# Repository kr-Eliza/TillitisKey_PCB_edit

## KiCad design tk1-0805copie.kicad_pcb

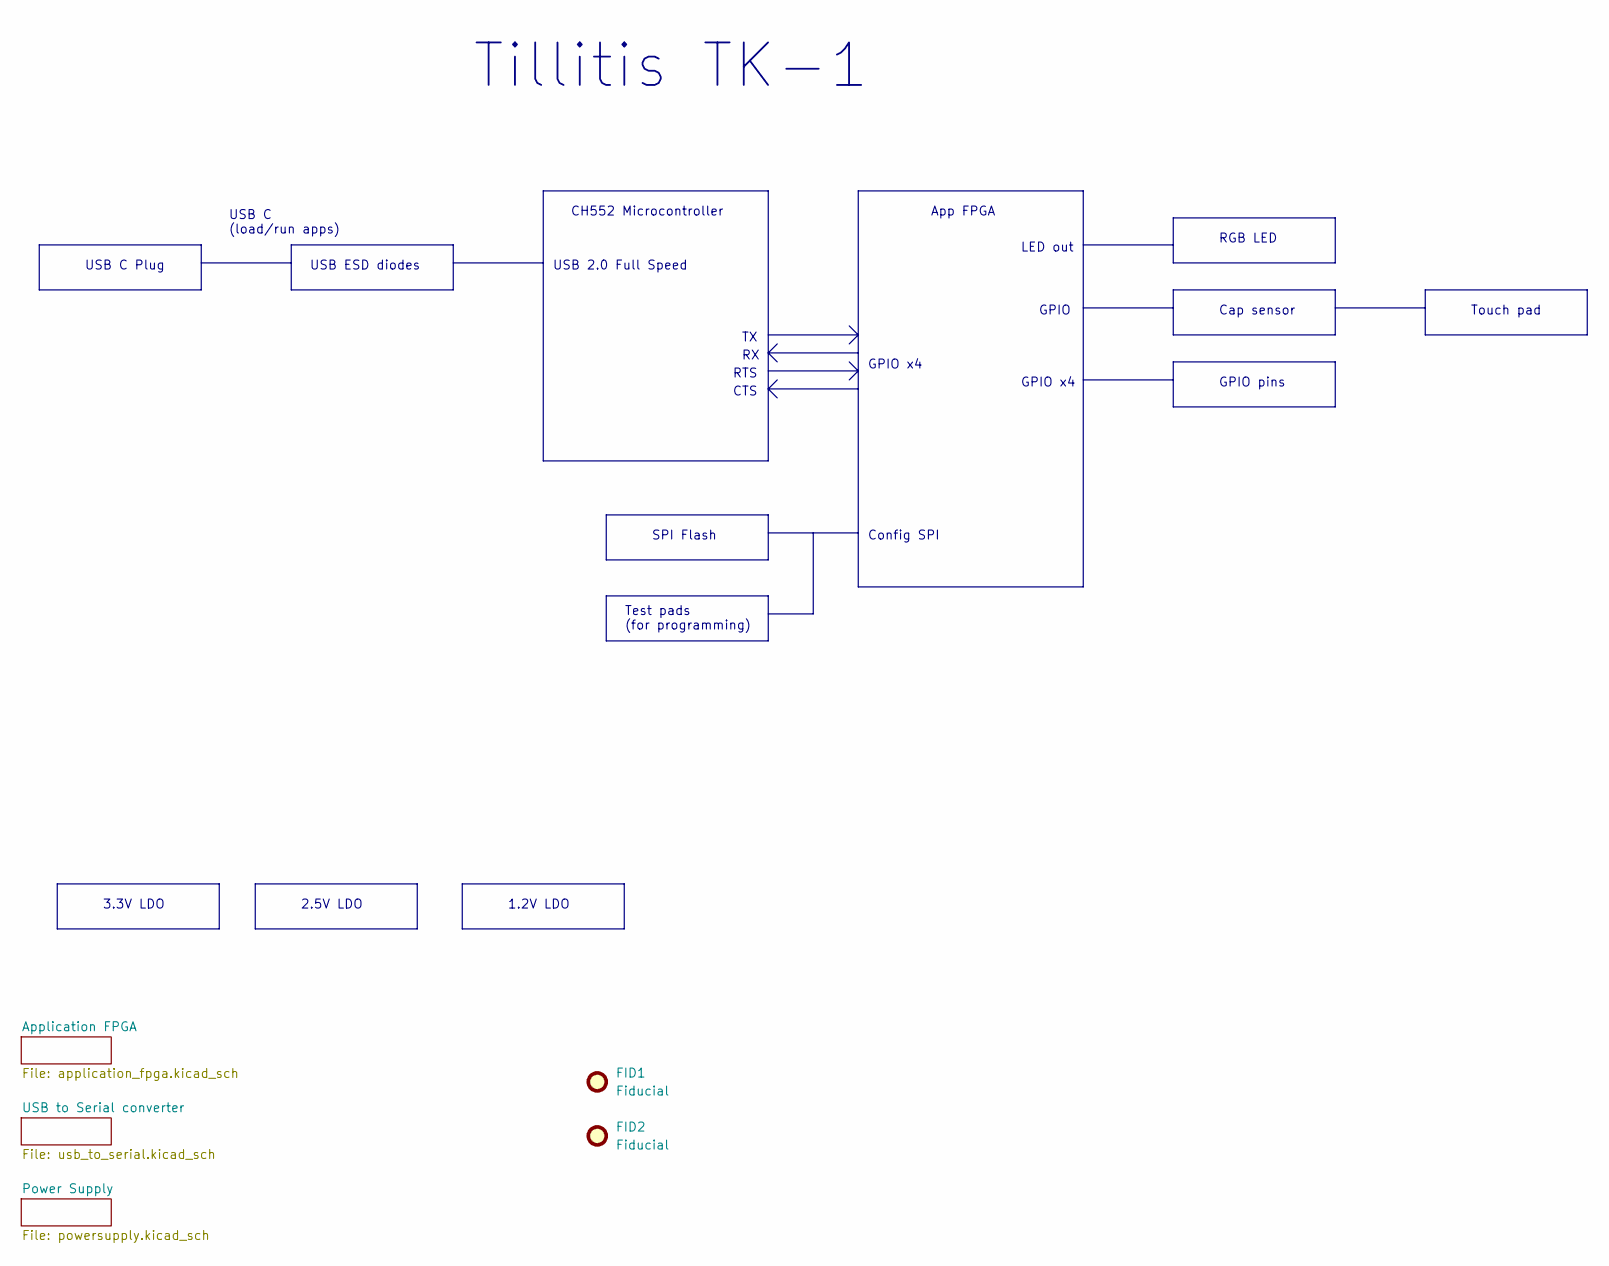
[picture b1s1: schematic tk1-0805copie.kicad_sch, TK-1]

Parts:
FID1, FID2: Fiducial; Fiducial_0.75mm_Mask1.5mm

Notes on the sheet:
USB ESD diodes
Touch pad
GPIO x4
GPIO pins
Cap sensor
USB 2.0 Full Speed
RTS
USB C Plug
CH552 Microcontroller
RGB LED
USB C (load/run apps)
1.2V LDO
3.3V LDO
CTS
2.5V LDO
App FPGA
Config SPI
Tillitis TK-1
SPI Flash
GPIO
LED out
Test pads (for programming)

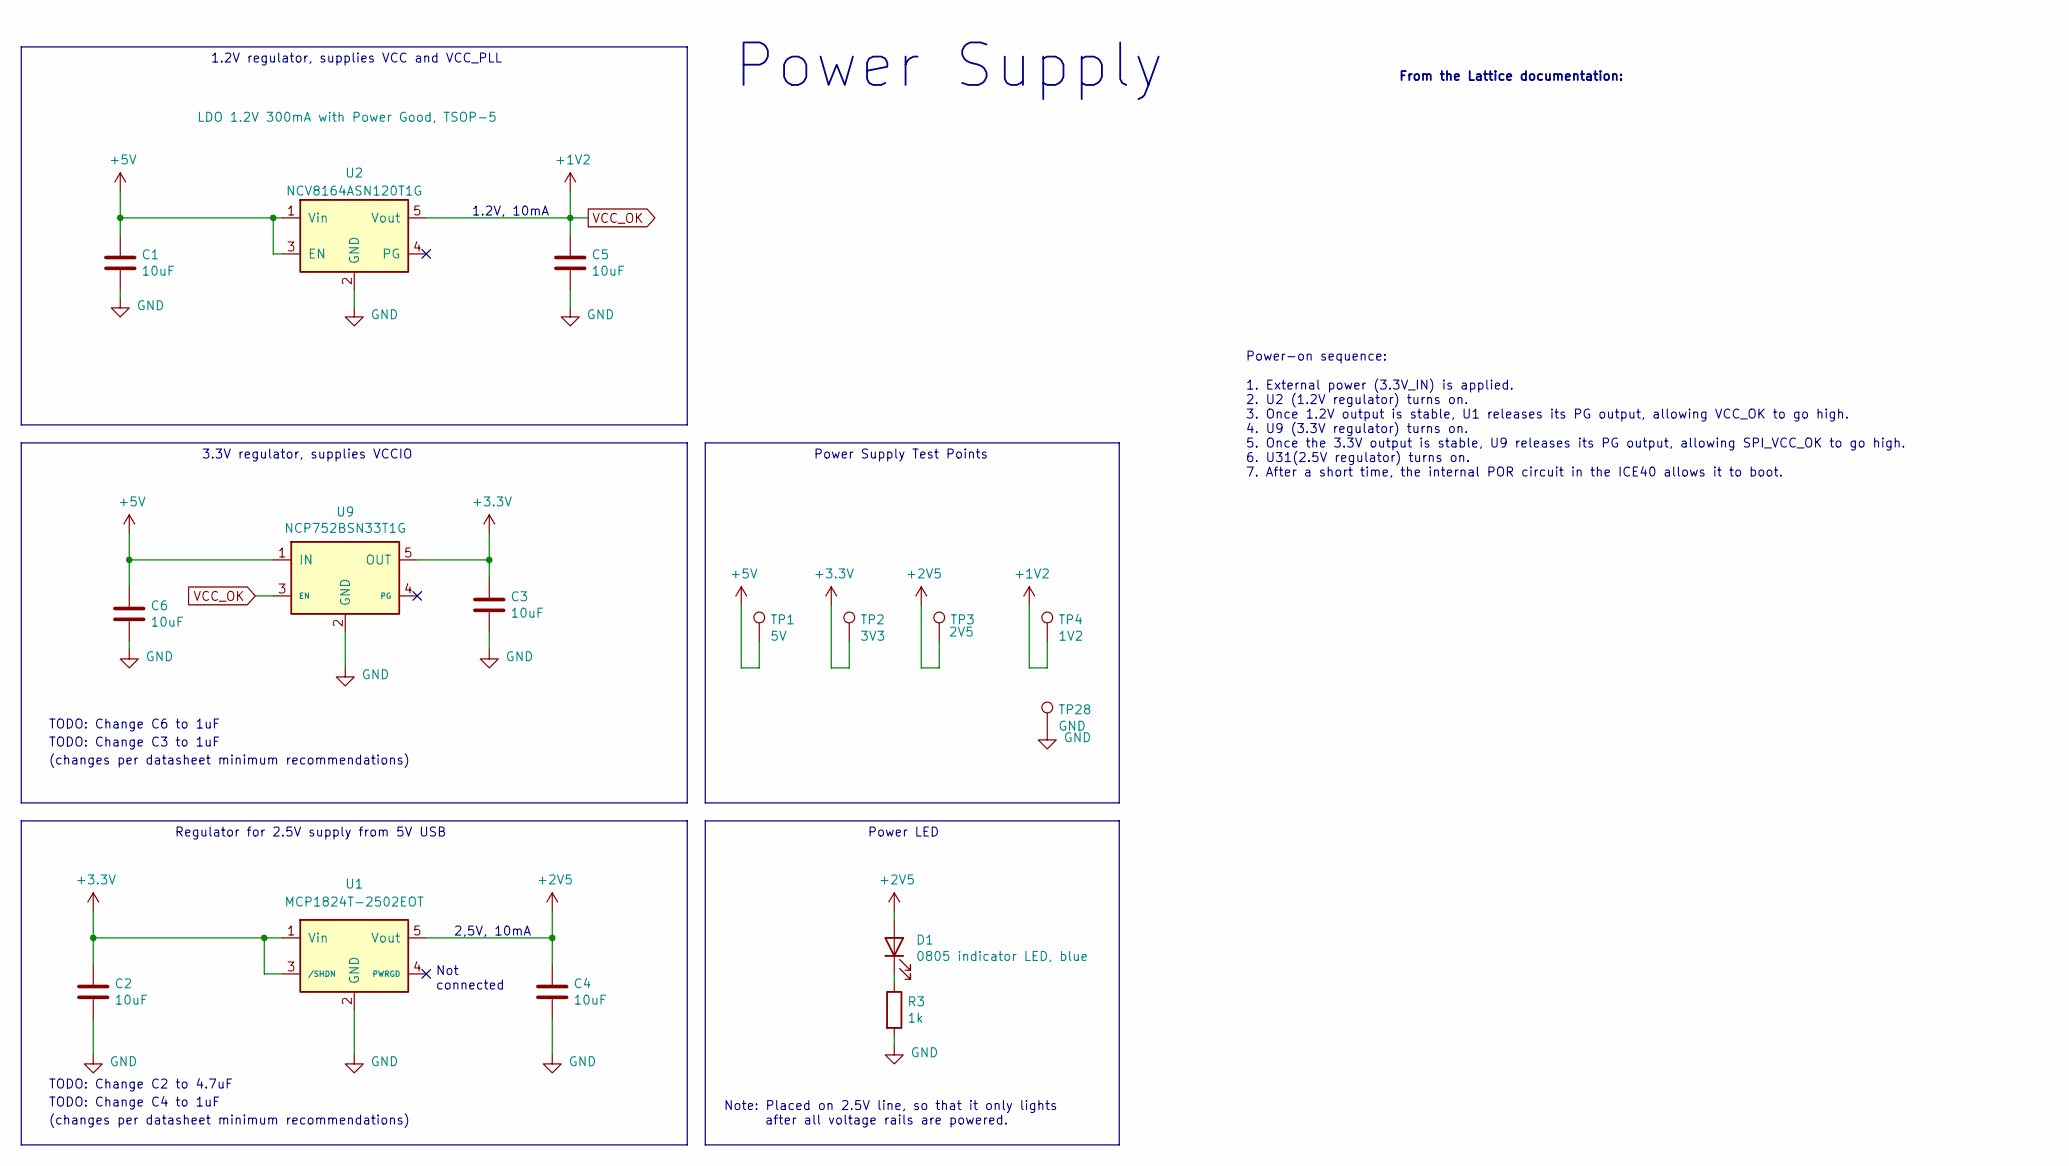
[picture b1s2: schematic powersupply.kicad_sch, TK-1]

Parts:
C1, C2, C3, C4, C5, C6: 10uF; C_0805_2012Metric_Pad1.18x1.45mm_HandSolder; Manufacturer Part Number CL21A106KPFNNNE; Mouser Part Number 187-CL21A106KPFNNNE
D1: 0805 indicator LED, blue; LED_0805_2012Metric_Pad1.15x1.40mm_HandSolder; Manufacturer Part Number LTST-S220TBKT; Mouser Part Number 859-LTST-S220TBKT
R3: 1k; R_0805_2012Metric_Pad1.20x1.40mm_HandSolder; Manufacturer Part Number RC0805FR-071KL; Mouser Part Number 603-RC0805FR-071KL
TP1: 5V; TestPoint_Pad_D1.0mm
TP2: 3V3; TestPoint_Pad_D1.0mm
TP3: 2V5; TestPoint_Pad_D1.0mm
TP4: 1V2; TestPoint_Pad_D1.0mm
TP28: GND; TestPoint_Pad_D1.0mm
U1: MCP1824T-2502EOT; SOT-23-5; Manufacturer Part Number MCP1824T-2502E/OT; Mouser Part Number 579-MCP1824T-2502E/OT
U2: NCV8164ASN120T1G; TSOP-5_1.65x3.05mm_P0.95mm; Manufacturer Part Number NCV8164ASN120T1G; Mouser Part Number 863-NCV8164ASN120T1G
U9: NCP752BSN33T1G; Manufacturer Part Number NCP752BSN33T1G; Mouser Part Number 863-NCP752BSN33T1G

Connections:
+2V5: C4.1, D1.2 (A), TP3.1, U1.5 (Vout); also elsewhere on the board
+3.3V: C2.1, C3.1, TP2.1, U1.1 (Vin), U1.3 (/SHDN), U9.5 (OUT); also elsewhere on the board
+5V: C1.1, C6.1, TP1.1, U2.1 (Vin), U2.3 (EN), U9.1 (IN); also elsewhere on the board
GND: C1.2, C2.2, C3.2, C4.2, C5.2, C6.2, R3.2, TP28.1, U1.2 (GND), U2.2 (GND), U9.2 (GND); also elsewhere on the board
unnamed: D1.1 (K), R3.1
VCC_OK: C5.1, TP4.1, U2.5 (Vout), U9.3 (EN); also elsewhere on the board

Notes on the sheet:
Power-on sequence: 1. External power (3.3V_IN) is applied. 2. U2 (1.2V regulator) turns on. 3. Once 1.2V output is stable, U1 releases its PG output, allowing VCC_OK to go high. 4. U9 (3.3V regulator) turns on. 5. Once the 3.3V output is stable, U9 releases its PG output, allowing SPI_VCC_OK to go 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
TODO: Change C2 to 4.7uF
(changes per datasheet minimum recommendations)
TODO: Change C6 to 1uF
2,5V, 10mA
Note: Placed on 2.5V line, so that it only lights after all voltage rails are powered.
TODO: Change C3 to 1uF
1.2V, 10mA
Power Supply
From the Lattice documentation:
1.2V regulator, supplies VCC and VCC_PLL
3.3V regulator, supplies VCCIO
TODO: Change C4 to 1uF
Not connected
Power Supply Test Points
Power LED
Regulator for 2.5V supply from 5V USB

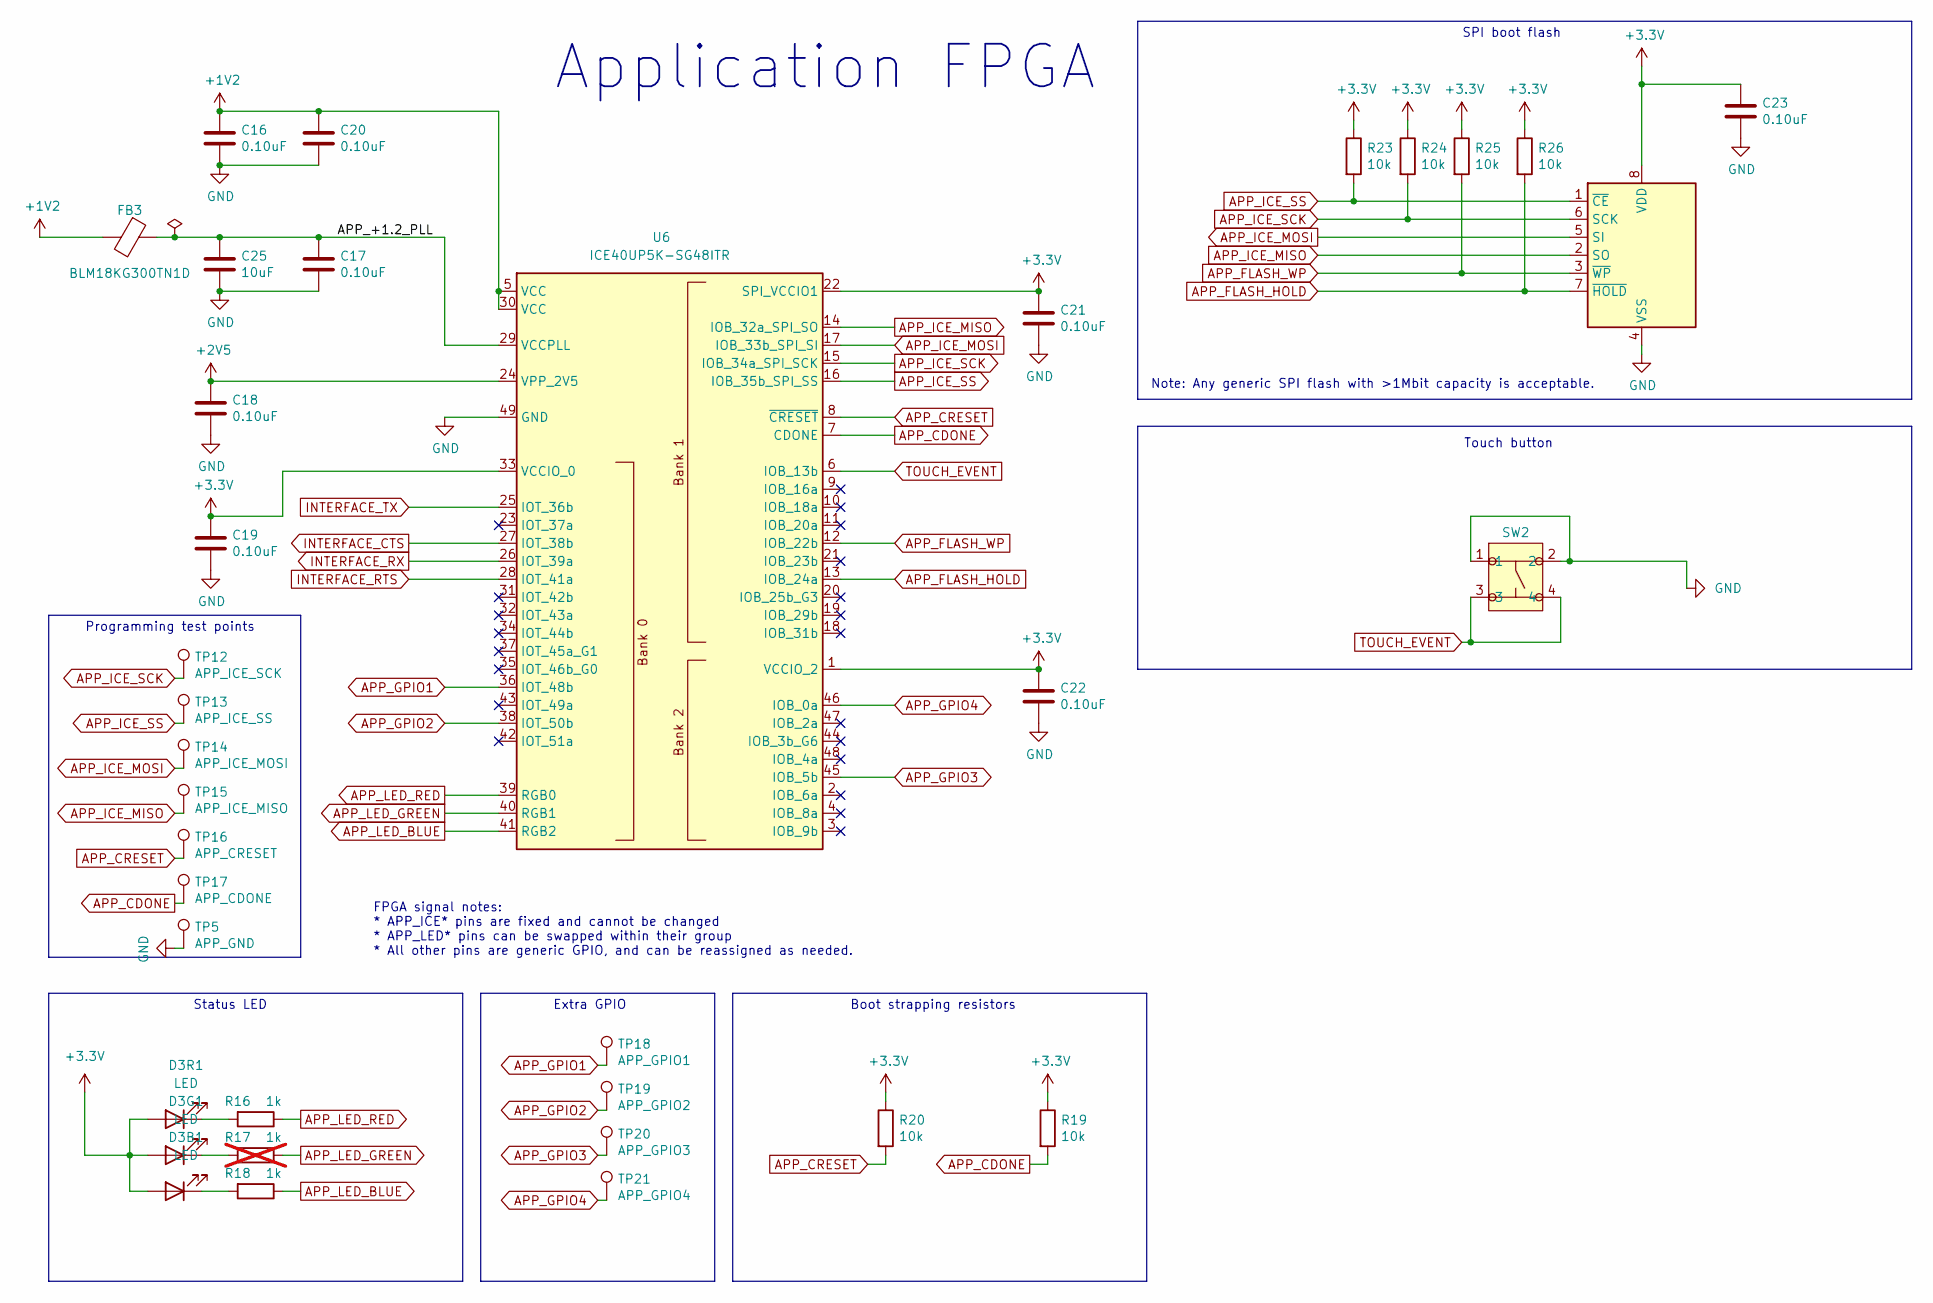
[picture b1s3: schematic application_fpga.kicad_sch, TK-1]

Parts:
C16, C17, C18, C19, C20, C21, C22, C23: 0.10uF; C_0805_2012Metric_Pad1.18x1.45mm_HandSolder; Manufacturer Part Number C0805C104K5RACTU; Mouser Part Number 80-C0805C104K5R
C25: 10uF; C_0805_2012Metric_Pad1.18x1.45mm_HandSolder; Manufacturer Part Number CL21A106KPFNNNE; Mouser Part Number 187-CL21A106KPFNNNE
D3B1: LED; LED_0805_2012Metric_Pad1.15x1.40mm_HandSolder; Manufacturer Part Number LTST-S220TBKT; Mouser Part Number 859-LTST-S220TBKT
D3G1: LED; LED_0805_2012Metric_Pad1.15x1.40mm_HandSolder; Manufacturer Part Number LTST-S270KGKT; Mouser Part Number 859-LTST-S270KGKT
D3R1: LED; LED_0805_2012Metric_Pad1.15x1.40mm_HandSolder; Manufacturer Part Number LTST-S270KRKT; Mouser Part Number 859-LTST-S270KRKT
FB3: BLM18KG300TN1D; Ferritbead_0603_1608Metric; Manufacturer Part Number BLM18KG300TN1D; Mouser Part Number 81-BLM18KG300TN1D
R16, R18: 1k; R_0805_2012Metric_Pad1.20x1.40mm_HandSolder; Manufacturer Part Number RC0805FR-071KL; Mouser Part Number 603-RC0805FR-071KL
R17: 1k; R_0805_2012Metric_Pad1.20x1.40mm_HandSolder; Manufacturer Part Number RC0805FR-071KL; Mouser Part Number 603-RC0805FR-071KL; not fitted
R19, R20, R23, R24, R25, R26: 10k; R_0805_2012Metric; Manufacturer Part Number RC0805FR-0710KL; Mouser Part Number 603-RC0805FR-0710KL
SW2: PTS526_SK15_SMTR2_LFS; PTS526SK15SMTR2LFS; Manufacturer_Part_Number PTS526 SK15 SMTR2 LFS; Mouser Part Number 611-PTS526SK15SMR2L
TP5: APP_GND; TestPoint_Pad_D1.0mm
TP12: APP_ICE_SCK; TestPoint_Pad_D1.0mm
TP13: APP_ICE_SS; TestPoint_Pad_D1.0mm
TP14: APP_ICE_MOSI; TestPoint_Pad_D1.0mm
TP15: APP_ICE_MISO; TestPoint_Pad_D1.0mm
TP16: APP_CRESET; TestPoint_Pad_D1.0mm
TP17: APP_CDONE; TestPoint_Pad_D1.0mm
TP18: APP_GPIO1; TestPoint_Pad_D1.0mm
TP19: APP_GPIO2; TestPoint_Pad_D1.0mm
TP20: APP_GPIO3; TestPoint_Pad_D1.0mm
TP21: APP_GPIO4; TestPoint_Pad_D1.0mm
U4: SST25VF080B-50-4x-S2Ax; SOIC-8_3.9x4.9mm_P1.27mm
U6: ICE40UP5K-SG48ITR; QFN-48-1EP_7x7mm_P0.5mm_EP5.3x5.3mm; Manufacturer Part Number ICE40UP5K-SG48I; Mouser Part Number 842-ICE40UP5K-SG48I

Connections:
+2V5: C18.1, U6.24 (VPP_2V5); also elsewhere on the board
+3.3V: C19.1, C21.1, C22.1, C23.1, D3B1.2 (A), D3G1.2 (A), D3R1.2 (A), R19.1, R20.1, R23.1, R24.1, R25.1, R26.1, U4.8 (VDD), U6.1 (VCCIO_2), U6.22 (SPI_VCCIO1), U6.33 (VCCIO_0); also elsewhere on the board
/Application FPGA/APP_+1.2_PLL: C17.1, C25.1, FB3.1, U6.29 (VCCPLL)
APP_CDONE: R19.2, TP17.1, U6.7 (CDONE)
APP_CRESET: R20.2, TP16.1, U6.8 (~CRESET)
APP_FLASH_HOLD: R26.2, U4.7 (~HOLD), U6.13 (IOB_24a)
APP_FLASH_WP: R25.2, U4.3 (~WP), U6.12 (IOB_22b)
APP_GPIO1: TP18.1, U6.36 (IOT_48b)
APP_GPIO2: TP19.1, U6.38 (IOT_50b)
APP_GPIO3: TP20.1, U6.45 (IOB_5b)
APP_GPIO4: TP21.1, U6.46 (IOB_0a)
APP_ICE_MISO: TP15.1, U4.2 (SO), U6.14 (IOB_32a_SPI_SO)
APP_ICE_MOSI: TP14.1, U4.5 (SI), U6.17 (IOB_33b_SPI_SI)
APP_ICE_SCK: R24.2, TP12.1, U4.6 (SCK), U6.15 (IOB_34a_SPI_SCK)
APP_ICE_SS: R23.2, TP13.1, U4.1 (~CE), U6.16 (IOB_35b_SPI_SS)
APP_LED_BLUE: R18.1, U6.41 (RGB2)
APP_LED_GREEN: R17.1, U6.40 (RGB1)
APP_LED_RED: R16.1, U6.39 (RGB0)
GND: C16.2, C17.2, C18.2, C19.2, C20.2, C21.2, C22.2, C23.2, C25.2, SW2.1, SW2.2, TP5.1, U4.4 (VSS), U6.49 (GND); also elsewhere on the board
INTERFACE_CTS: U6.27 (IOT_38b); also elsewhere on the board
INTERFACE_RTS: U6.28 (IOT_41a); also elsewhere on the board
INTERFACE_RX: U6.26 (IOT_39a); also elsewhere on the board
INTERFACE_TX: U6.25 (IOT_36b); also elsewhere on the board
unnamed: D3B1.1 (K), R18.2
unnamed: D3G1.1 (K), R17.2
unnamed: D3R1.1 (K), R16.2
TOUCH_EVENT: SW2.3, SW2.4, U6.6 (IOB_13b)
VCC_OK: C16.1, C20.1, FB3.2, U6.5 (VCC), U6.30 (VCC); also elsewhere on the board

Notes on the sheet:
Application FPGA
SPI boot flash
FPGA signal notes: * APP_ICE* pins are fixed and cannot be changed * APP_LED* pins can be swapped within their group * All other pins are generic GPIO, and can be reassigned as needed.
Boot strapping resistors
Touch button
Status LED
Programming test points
Note: Any generic SPI flash with >1Mbit capacity is acceptable.
Extra GPIO

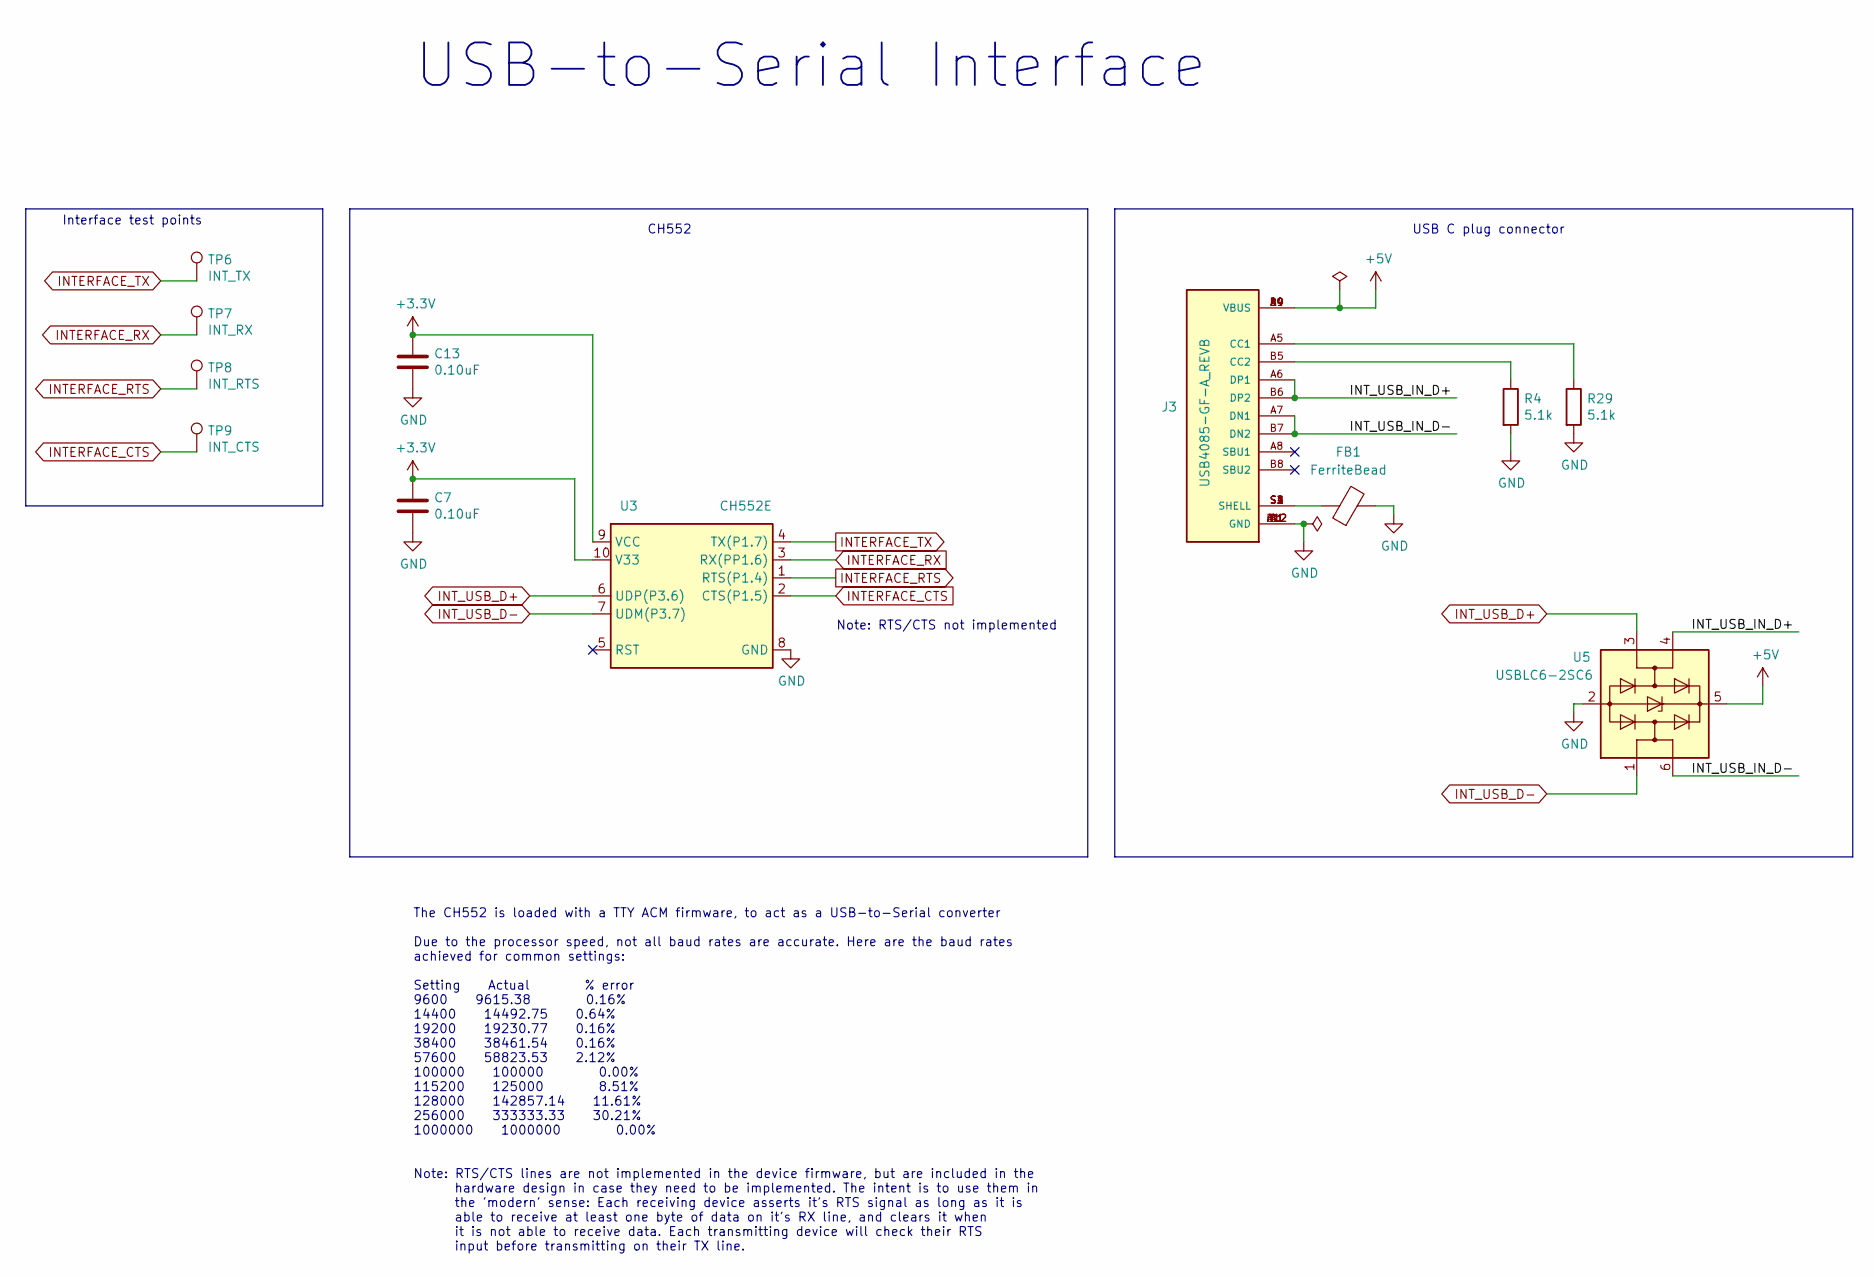
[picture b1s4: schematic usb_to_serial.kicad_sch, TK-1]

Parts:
C7, C13: 0.10uF; C_0805_2012Metric_Pad1.18x1.45mm_HandSolder; Manufacturer Part Number C0805C104K5RACTU; Mouser Part Number 80-C0805C104K5R
FB1: FerriteBead; R_0805_2012Metric_Pad1.20x1.40mm_HandSolder
J3: USB4085-GF-A_REVB; GCT_USB4085-GF-A_REVB; PARTREV B
R4, R29: 5.1k; R_0805_2012Metric_Pad1.20x1.40mm_HandSolder; Manufacturer Part Number RC0805FR-075K1L; Mouser Part Number 603-RC0805FR-075K1L
TP6: INT_TX; TestPoint_Pad_D1.0mm
TP7: INT_RX; TestPoint_Pad_D1.0mm
TP8: INT_RTS; TestPoint_Pad_D1.0mm
TP9: INT_CTS; TestPoint_Pad_D1.0mm
U3: CH552E; MSOP-10_3x3mm_P0.5mm; Manufacturer Part Number CH552E; Mouser Part Number 556-AT42QT1010-TSHR
U5: USBLC6-2SC6; SOT-23-6; Manufacturer Part Number USBLC6-2SC6; Mouser Part Number 511-USBLC6-2SC6

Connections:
+3.3V: C7.1, C13.1, U3.9 (VCC), U3.10 (V33); also elsewhere on the board
+5V: J3.A4 (VBUS), J3.A9 (VBUS), J3.B4 (VBUS), J3.B9 (VBUS), U5.5 (VBUS); also elsewhere on the board
/USB to Serial converter/INT_USB_IN_D+: J3.A6 (DP1), J3.B6 (DP2), U5.4 (I/O2)
/USB to Serial converter/INT_USB_IN_D-: J3.A7 (DN1), J3.B7 (DN2), U5.6 (I/O1)
GND: C7.2, C13.2, FB1.2, J3.A1 (GND), J3.A12 (GND), J3.B1 (GND), J3.B12 (GND), R4.2, R29.2, U3.8 (GND), U5.2 (GND); also elsewhere on the board
INTERFACE_CTS: TP9.1, U3.2 (CTS(P1.5)); also elsewhere on the board
INTERFACE_RTS: TP8.1, U3.1 (RTS(P1.4)); also elsewhere on the board
INTERFACE_RX: TP7.1, U3.3 (RX(PP1.6)); also elsewhere on the board
INTERFACE_TX: TP6.1, U3.4 (TX(P1.7)); also elsewhere on the board
INT_USB_D+: U3.6 (UDP(P3.6)), U5.3 (I/O2)
INT_USB_D-: U3.7 (UDM(P3.7)), U5.1 (I/O1)
unnamed: FB1.1, J3.S1 (SHELL), J3.S2 (SHELL), J3.S3 (SHELL), J3.S4 (SHELL)
unnamed: J3.A5 (CC1), R29.1
unnamed: J3.B5 (CC2), R4.1

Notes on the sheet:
USB C plug connector
CH552
USB-to-Serial Interface
The CH552 is loaded with a TTY ACM firmware, to act as a USB-to-Serial converter Due to the processor speed, not all baud rates are accurate. Here are the baud rates achieved for common settings: Setting Actual % error 9600 9615.38 0.16% 14400 14492.75 0.64% 19200 19230.77 0.16% 38400 38461.54 0.16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
Interface test points
Note: RTS/CTS not implemented

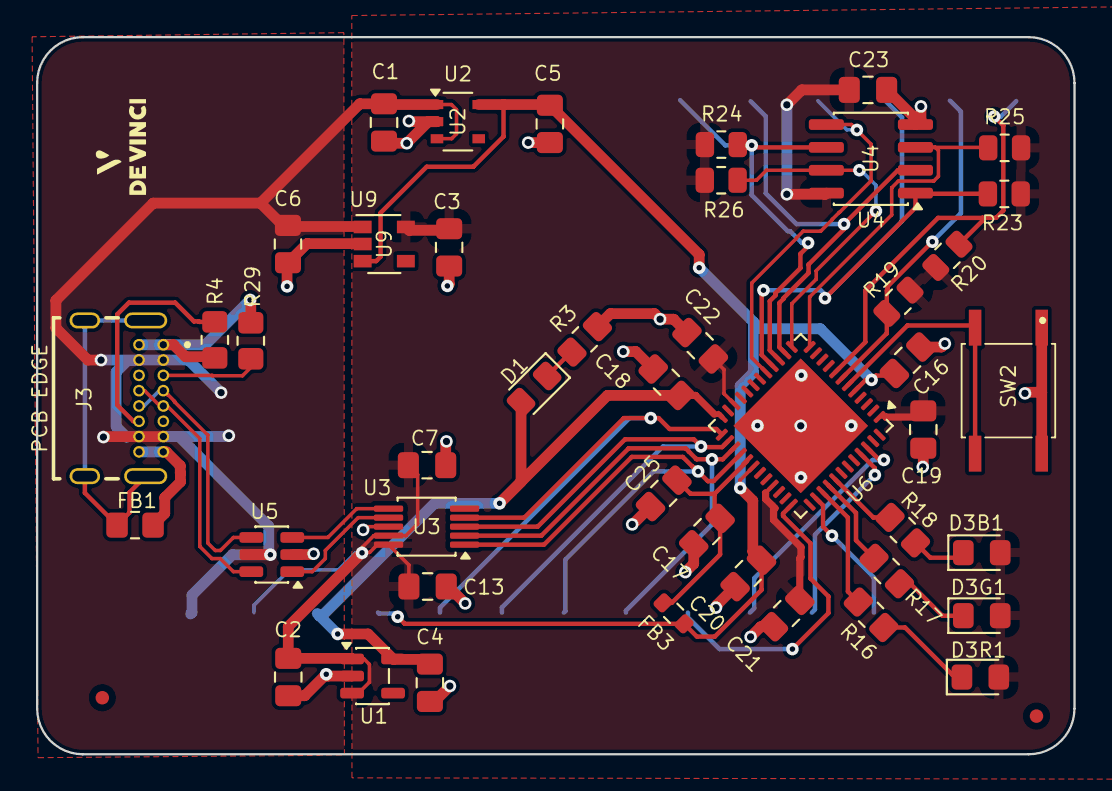
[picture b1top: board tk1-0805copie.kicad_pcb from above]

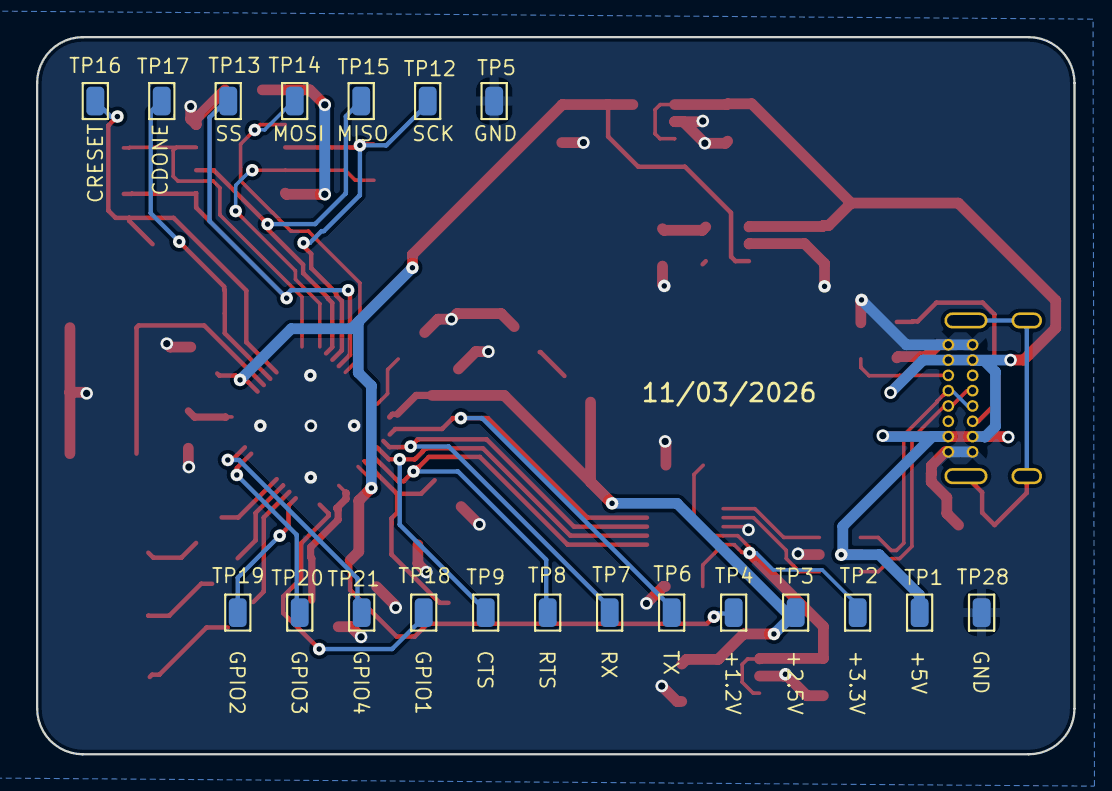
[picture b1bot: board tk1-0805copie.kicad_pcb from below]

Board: 2 copper layers, 57.6 x 39.8 mm, 66 parts (20 on the bottom side), 37 nets.

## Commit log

2026-03-02 Initial import of KiCad project
2026-03-02 Update KiCad project
2026-03-10 Mise à jour du projet
2026-03-10 Clean project files
2026-03-12 Version sent to fabrication
2026-03-12 Missing 3D models added
